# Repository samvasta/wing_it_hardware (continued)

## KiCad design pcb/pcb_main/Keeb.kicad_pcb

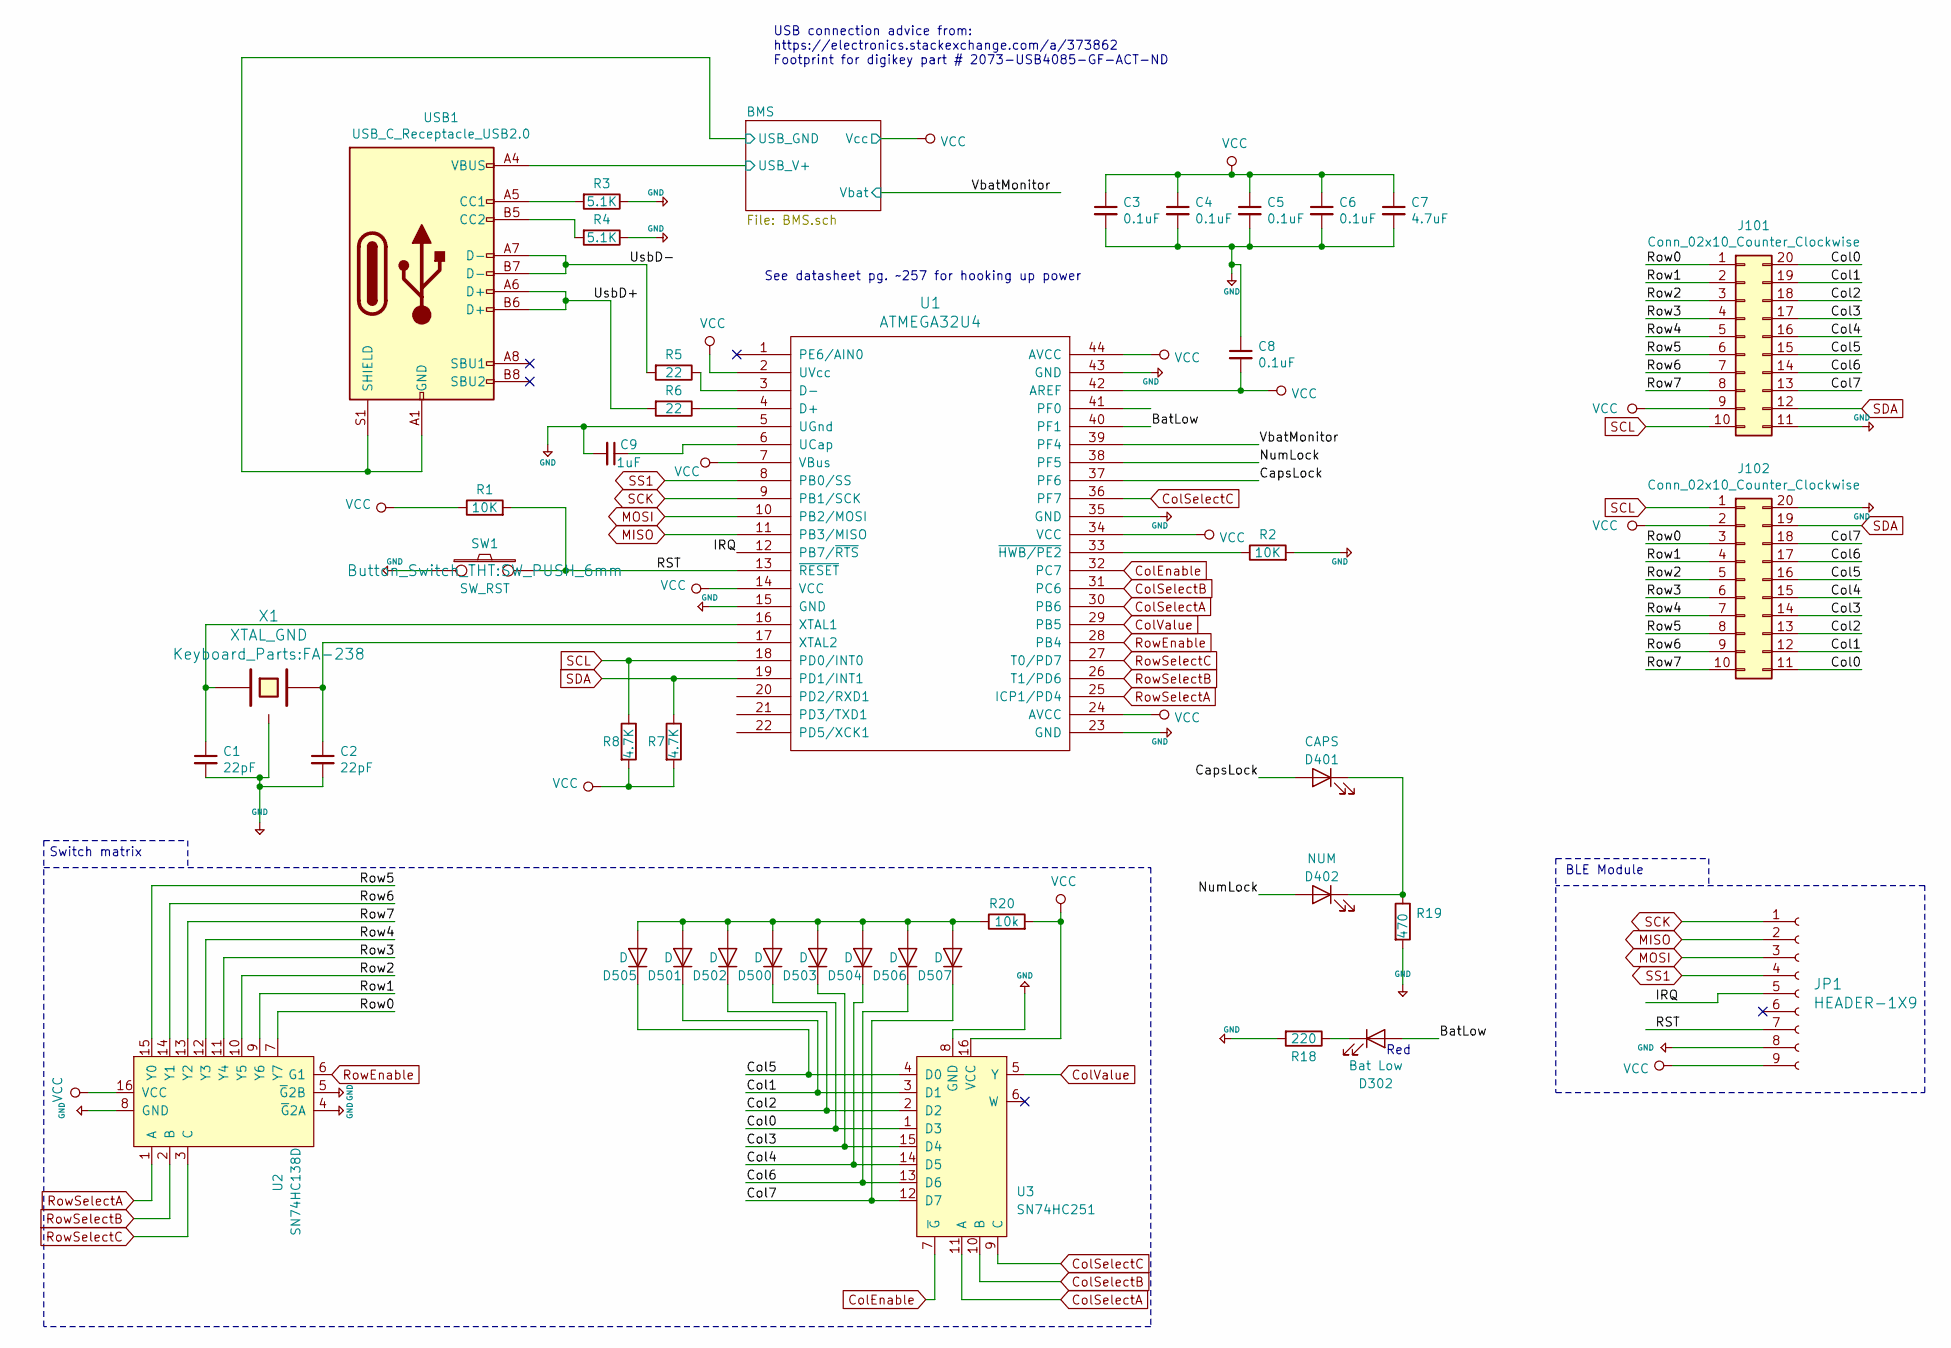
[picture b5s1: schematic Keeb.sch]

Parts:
C1, C2: 22pF; C_0805_2012Metric_Pad1.15x1.40mm_HandSolder
C3, C4, C5, C6, C8: 0.1uF; C_0805_2012Metric_Pad1.15x1.40mm_HandSolder
C7: 4.7uF; C_0805_2012Metric_Pad1.15x1.40mm_HandSolder
C9: 1uF; C_0805_2012Metric_Pad1.15x1.40mm_HandSolder
D302: Bat Low; LED_0805_2012Metric_Pad1.15x1.40mm_HandSolder
D401: CAPS; LED_0805_2012Metric_Pad1.15x1.40mm_HandSolder
D402: NUM; LED_0805_2012Metric_Pad1.15x1.40mm_HandSolder
D500, D501, D502, D503, D504, D505, D506, D507: D; D_0805_2012Metric_Pad1.15x1.40mm_HandSolder
J101, J102: Conn_02x10_Counter_Clockwise; Backplane_Connector_Hirose_PCN_20pos_Plug
JP1: HEADER-1X9; Adafruit_BLE_SPI_wire_tht
R1, R2: 10K; R_0805_2012Metric_Pad1.15x1.40mm_HandSolder
R3, R4: 5.1K; R_0805_2012Metric_Pad1.15x1.40mm_HandSolder
R5, R6: 22; R_0805_2012Metric_Pad1.15x1.40mm_HandSolder
R7, R8: 4.7K; R_0805_2012Metric_Pad1.15x1.40mm_HandSolder
R18: 220; R_0805_2012Metric_Pad1.15x1.40mm_HandSolder
R19: 470; R_0805_2012Metric_Pad1.15x1.40mm_HandSolder
R20: 10k; R_0805_2012Metric_Pad1.15x1.40mm_HandSolder
SW1: SW_RST; SW_PUSH_6mm
U1: ATMEGA32U4; ATMEGA32U4-AU
U2: SN74HC138D‎; SN74HC_package_d_soic
U3: SN74HC251; SN74HC_package_d_soic
USB1: USB_C_Receptacle_USB2.0; USB_C_Receptacle_GCT_USB4085
X1: XTAL_GND; FA-238

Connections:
/BMS/USB_V+: USB1.A4 (VBUS), USB1.A9 (VBUS), USB1.B4 (VBUS), USB1.B9 (VBUS); also elsewhere on the board
/BatLow: D302.2 (A), U1.40 (PF1)
/CapsLock: D401.2 (A), U1.37 (PF6)
/Col0: D500.1 (K), J101.20, J102.11, U3.1 (D3)
/Col1: D501.1 (K), J101.19, J102.12, U3.3 (D1)
/Col2: D502.1 (K), J101.18, J102.13, U3.2 (D2)
/Col3: D503.1 (K), J101.17, J102.14, U3.15 (D4)
/Col4: D504.1 (K), J101.16, J102.15, U3.14 (D5)
/Col5: D505.1 (K), J101.15, J102.16, U3.4 (D0)
/Col6: D506.1 (K), J101.14, J102.17, U3.13 (D6)
/Col7: D507.1 (K), J101.13, J102.18, U3.12 (D7)
/IRQ: JP1.5, U1.12 (PB7/~RTS)
/NumLock: D402.2 (A), U1.38 (PF5)
/RST: JP1.7, R1.2, SW1.2, U1.13 (~RESET)
/Row0: J101.1, J102.3, U2.7 (Y7)
/Row1: J101.2, J102.4, U2.9 (Y6)
/Row2: J101.3, J102.5, U2.10 (Y5)
/Row3: J101.4, J102.6, U2.11 (Y4)
/Row4: J101.5, J102.7, U2.12 (Y3)
/Row5: J101.6, J102.8, U2.15 (Y0)
/Row6: J101.7, J102.9, U2.14 (Y1)
/Row7: J101.8, J102.10, U2.13 (Y2)
/UsbD+: R6.2, USB1.A6 (D+), USB1.B6 (D+)
/UsbD-: R5.2, USB1.A7 (D-), USB1.B7 (D-)
/VbatMonitor: U1.39 (PF4); also elsewhere on the board
ColEnable: U1.32 (PC7), U3.7 (~G)
ColSelectA: U1.30 (PB6), U3.11 (A)
ColSelectB: U1.31 (PC6), U3.10 (B)
ColSelectC: U1.36 (PF7), U3.9 (C)
ColValue: U1.29 (PB5), U3.5 (Y)
GND: C1.2, C2.2, C3.2, C4.2, C5.2, C6.2, C7.2, C8.1, C9.2, J101.11, J102.20, JP1.8, R2.2, R3.1, R4.1, R18.2, R19.2, SW1.1, U1.5 (UGnd), U1.15 (GND), U1.23 (GND), U1.35 (GND), U1.43 (GND), U2.4 (~G~2A), U2.5 (~G~2B), U2.8 (GND), U3.8 (GND), USB1.A1 (GND), USB1.A12 (GND), USB1.B1 (GND), USB1.B12 (GND), USB1.S1 (SHIELD), X1.3; also elsewhere on the board
MISO: JP1.2, U1.11 (PB3/MISO)
MOSI: JP1.3, U1.10 (PB2/MOSI)
unnamed: C1.1, U1.16 (XTAL1), X1.1
unnamed: C2.1, U1.17 (XTAL2), X1.2
unnamed: C9.1, U1.6 (UCap)
unnamed: D302.1 (K), R18.1
unnamed: D401.1 (K), D402.1 (K), R19.1
unnamed: D500.2 (A), D501.2 (A), D502.2 (A), D503.2 (A), D504.2 (A), D505.2 (A), D506.2 (A), D507.2 (A), R20.1
unnamed: R2.1, U1.33 (~HWB/PE2)
unnamed: R3.2, USB1.A5 (CC1)
unnamed: R4.2, USB1.B5 (CC2)
unnamed: R5.1, U1.3 (D-)
unnamed: R6.1, U1.4 (D+)
RowEnable: U1.28 (PB4), U2.6 (G1)
RowSelectA: U1.25 (ICP1/PD4), U2.1 (A)
RowSelectB: U1.26 (T1/PD6), U2.2 (B)
RowSelectC: U1.27 (T0/PD7), U2.3 (C)
SCK: JP1.1, U1.9 (PB1/SCK)
SCL: J101.10, J102.1, R8.1, U1.18 (PD0/INT0)
SDA: J101.12, J102.19, R7.1, U1.19 (PD1/INT1)
SS1: JP1.4, U1.8 (PB0/SS)
VCC: C3.1, C4.1, C5.1, C6.1, C7.1, C8.2, J101.9, J102.2, JP1.9, R1.1, R7.2, R8.2, R20.2, U1.2 (UVcc), U1.7 (VBus), U1.14 (VCC), U1.24 (AVCC), U1.34 (VCC), U1.42 (AREF), U1.44 (AVCC), U2.16 (VCC), U3.16 (VCC); also elsewhere on the board

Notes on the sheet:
USB connection advice from: https://electronics.stackexchange.com/a/373862 Footprint for digikey part # 2073-USB4085-GF-ACT-ND
See datasheet pg. ~~257 for hooking up power
Switch matrix
BLE Module
Red

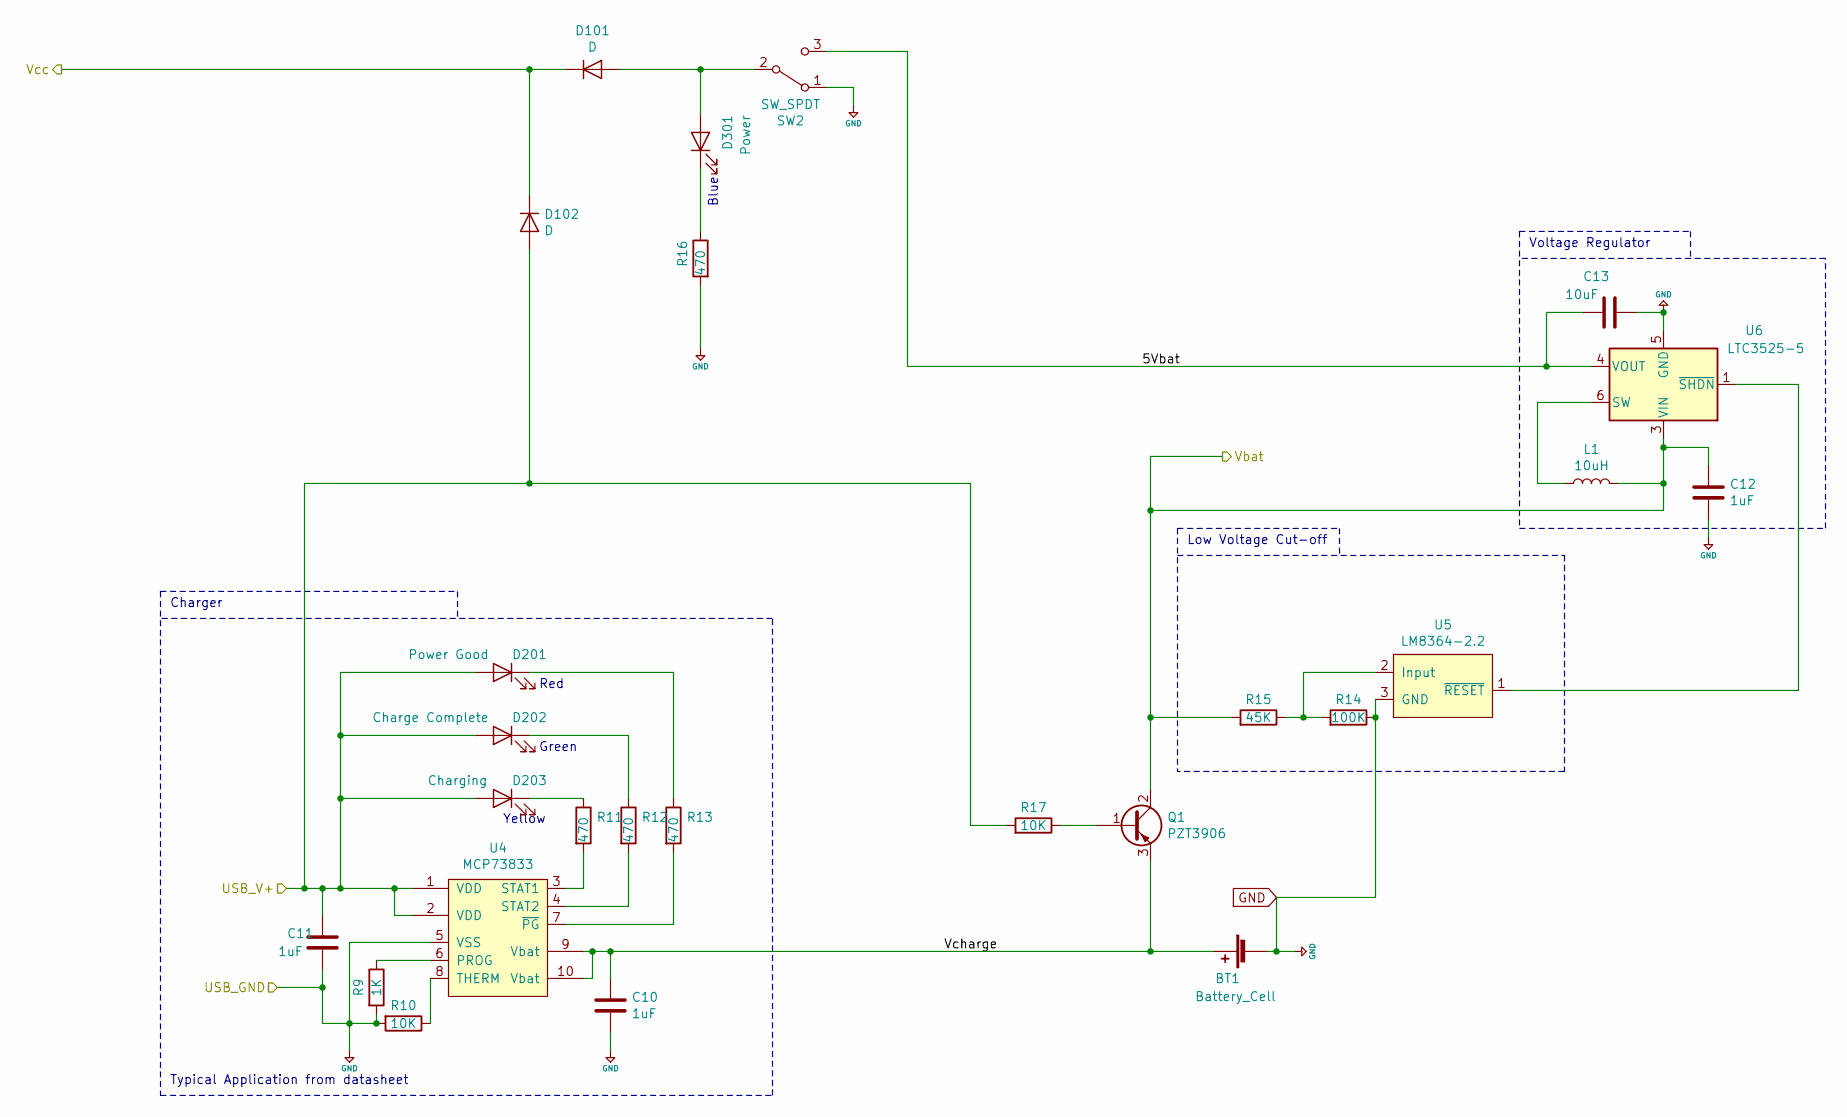
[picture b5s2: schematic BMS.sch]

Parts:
BT1: Battery_Cell; BatteryHolder_Keystone_1088_1xAA
C10, C11, C12: 1uF; C_0805_2012Metric_Pad1.15x1.40mm_HandSolder
C13: 10uF; C_0805_2012Metric_Pad1.15x1.40mm_HandSolder
D101, D102: D; D_MiniMELF_Handsoldering_Shorter_Pads
D201: Power Good; LED_0805_2012Metric_Pad1.15x1.40mm_HandSolder
D202: Charge Complete; LED_0805_2012Metric_Pad1.15x1.40mm_HandSolder
D203: Charging; LED_0805_2012Metric_Pad1.15x1.40mm_HandSolder
D301: Power; LED_0805_2012Metric_Pad1.15x1.40mm_HandSolder
L1: 10uH; L_0805_2012Metric_Pad1.15x1.40mm_HandSolder
Q1: PZT3906; SOT-223
R9: 1K; R_0805_2012Metric_Pad1.15x1.40mm_HandSolder
R10, R17: 10K; R_0805_2012Metric_Pad1.15x1.40mm_HandSolder
R11, R12, R13, R16: 470; R_0805_2012Metric_Pad1.15x1.40mm_HandSolder
R14: 100K; R_0805_2012Metric_Pad1.15x1.40mm_HandSolder
R15: 45K; R_0805_2012Metric_Pad1.15x1.40mm_HandSolder
SW2: SW_SPDT; SW_Slide_C&K_JS102011SAQN
U4: MCP73833; MCP73833T-AMI-UN
U5: LM8364-2.2; SOT-23-5_HandSoldering
U6: LTC3525-5; SOT-363_SC-70-6_Handsoldering

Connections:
/BMS/5Vbat: C13.2, SW2.3 (C), U6.4 (VOUT)
/BMS/USB_V+: C11.1, D102.2 (A), D201.2 (A), D202.2 (A), D203.2 (A), R17.2, U4.1 (VDD), U4.2 (VDD); also elsewhere on the board
/BMS/Vcharge: BT1.1 (+), C10.1, Q1.3 (E), U4.9 (Vbat), U4.10 (Vbat)
/VbatMonitor: C12.1, L1.1, Q1.2 (C), Q1.4 (C), R15.2, U6.3 (VIN); also elsewhere on the board
GND: BT1.2 (-), C10.2, C11.2, C12.2, C13.1, R9.2, R10.2, R14.1, R16.2, SW2.1 (A), U4.5 (VSS), U5.3 (GND), U6.2 (GND), U6.5 (GND); also elsewhere on the board
unnamed: D101.2 (A), D301.2 (A), SW2.2 (B)
unnamed: D201.1 (K), R13.1
unnamed: D202.1 (K), R12.1
unnamed: D203.1 (K), R11.1
unnamed: D301.1 (K), R16.1
unnamed: L1.2, U6.6 (SW)
unnamed: Q1.1 (B), R17.1
unnamed: R9.1, U4.6 (PROG)
unnamed: R10.1, U4.8 (THERM)
unnamed: R11.2, U4.3 (STAT1)
unnamed: R12.2, U4.4 (STAT2)
unnamed: R13.2, U4.7 (~PG)
unnamed: R14.2, R15.1, U5.2 (Input)
unnamed: U5.1 (~RESET), U6.1 (~SHDN)
VCC: D101.1 (K), D102.1 (K); also elsewhere on the board

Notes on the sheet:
Typical Application from datasheet
Charger
Low Voltage Cut-off
Green
Red
Yellow
Blue
Voltage Regulator

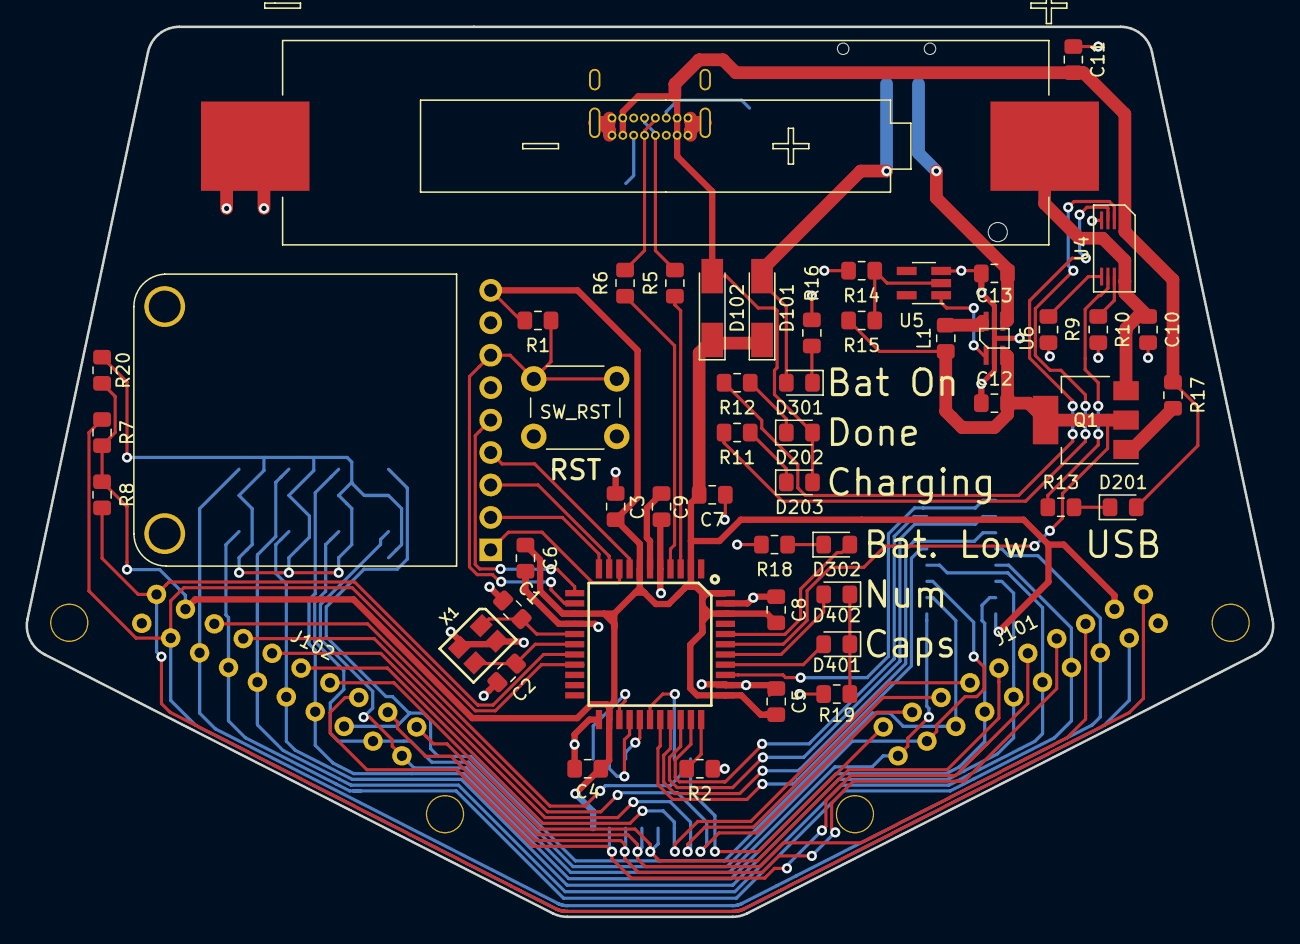
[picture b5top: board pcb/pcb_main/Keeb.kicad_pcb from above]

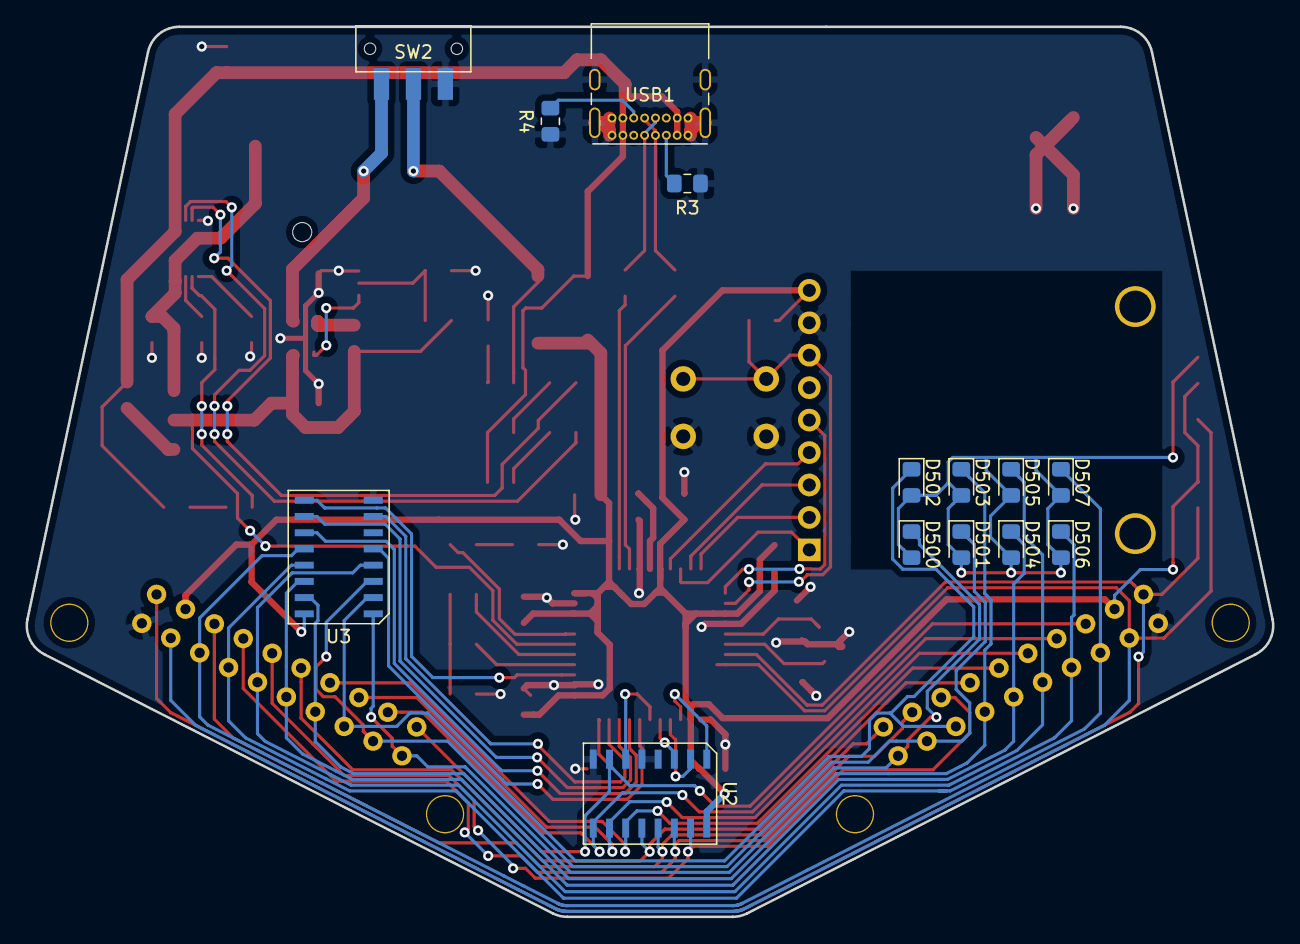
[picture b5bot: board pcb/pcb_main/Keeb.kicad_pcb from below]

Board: 2 copper layers, 97.6 x 69.7 mm, 66 parts (15 on the bottom side), 69 nets.

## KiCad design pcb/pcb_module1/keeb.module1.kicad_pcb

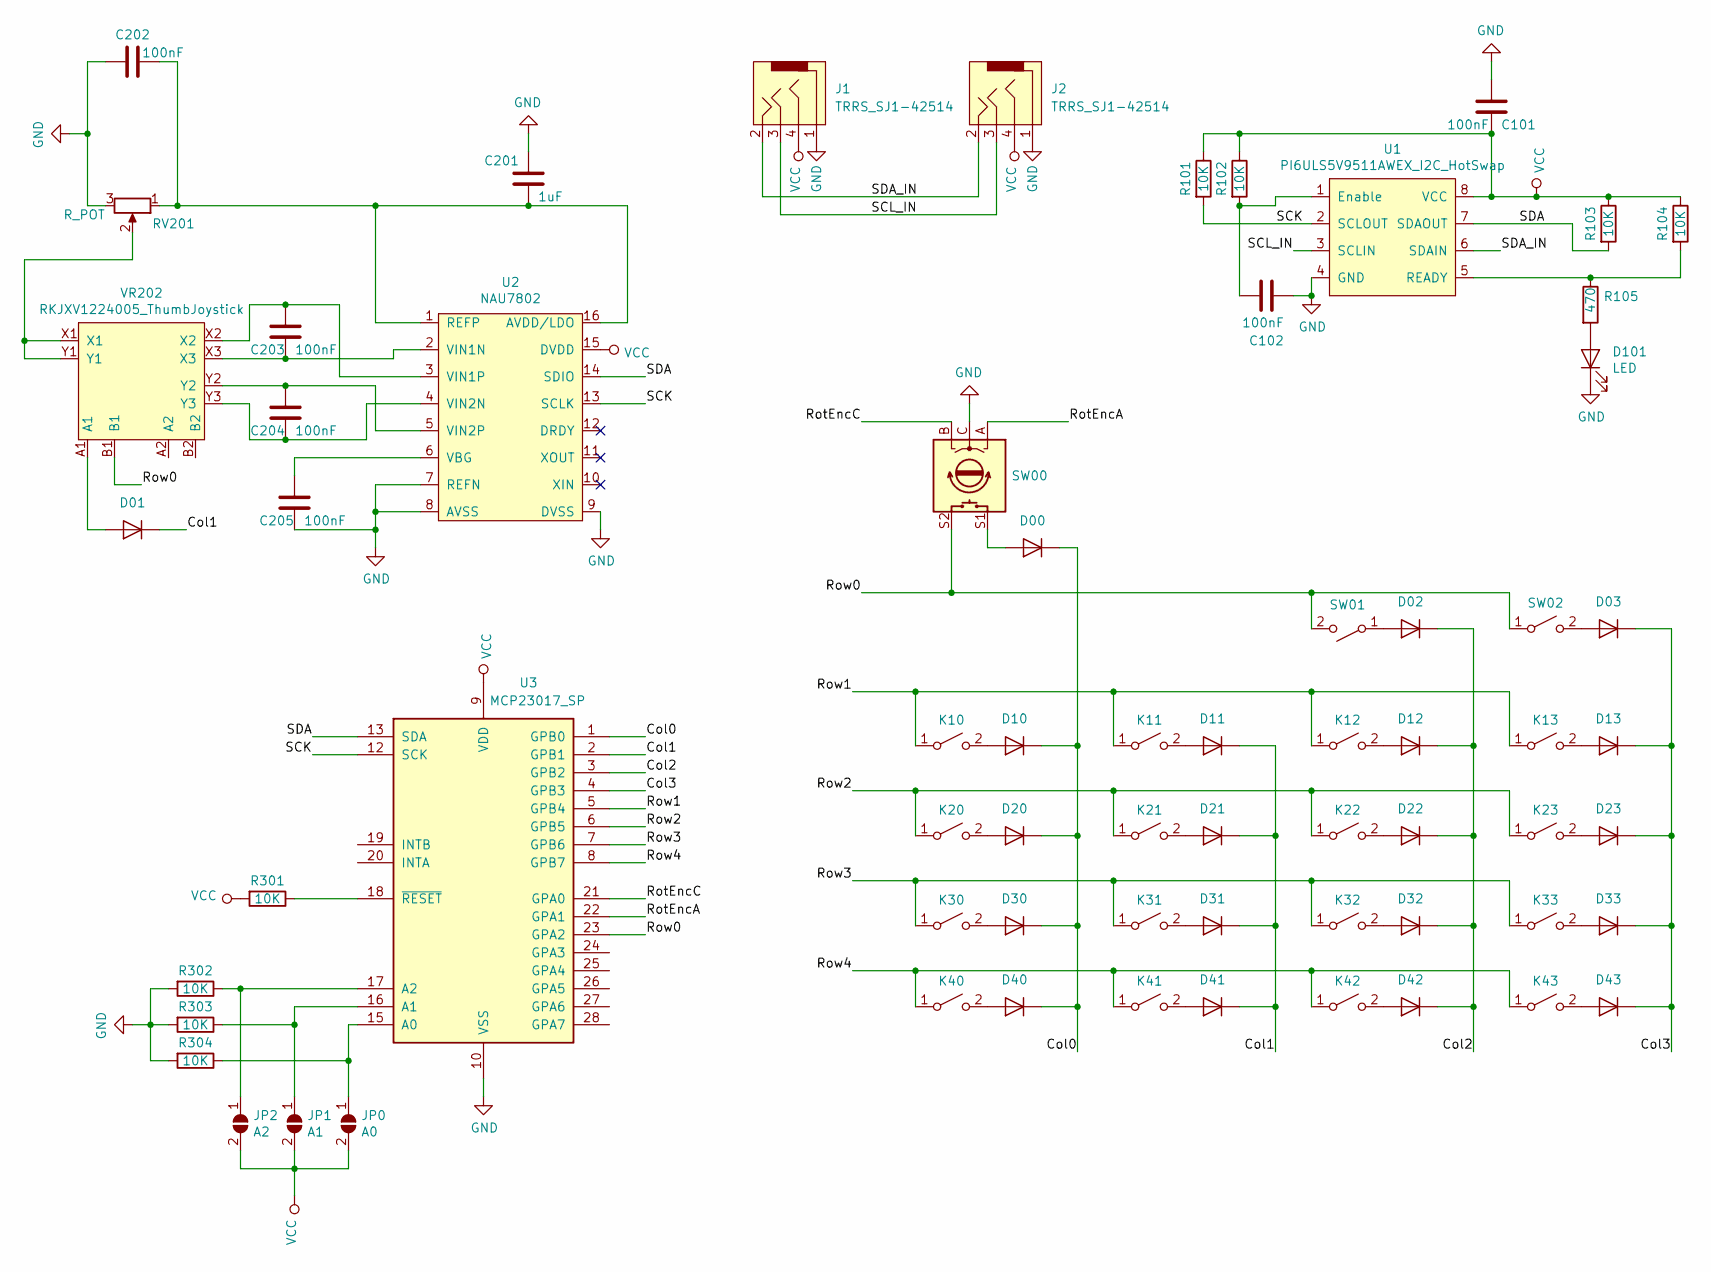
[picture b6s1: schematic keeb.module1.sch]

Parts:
C101, C102, C202, C203, C204, C205: 100nF; C_0805_2012Metric_Pad1.15x1.40mm_HandSolder
C201: 1uF; C_0805_2012Metric_Pad1.15x1.40mm_HandSolder
D00, D01, D02, D03, D10, D11, D12, D13, D20, D21, D22, D23, D30, D31, D32, D33, D40, D41, D42, D43: D; D_A-405_P7.62mm_Horizontal
D101: LED; D_0805_2012Metric_Pad1.15x1.40mm_HandSolder
J1, J2: TRRS_SJ1-42514; 3.5mm_Cut_out
JP0: A0; SolderJumper-2_P1.3mm_Open_RoundedPad1.0x1.5mm
JP1: A1; SolderJumper-2_P1.3mm_Open_RoundedPad1.0x1.5mm
JP2: A2; SolderJumper-2_P1.3mm_Open_RoundedPad1.0x1.5mm
K10, K11, K12, K13, K20, K21, K22, K23, K30, K31, K32, K33, K40, K41, K42, K43: SW_SPST; Kailh_socket_vias
R101, R102, R103, R104, R301, R302, R303, R304: 10K; Resistor-Compact
R105: 470; Resistor-Compact
RV201: R_POT; SlidePot_PS45M
SW00: Rotary_Encoder_Switch; PEC12R-4xxxF-Sxxxx_Rotary_Encoder
SW01, SW02: SW_SPST; B3J-1100_Switch
U1: PI6ULS5V9511AWEX_I2C_HotSwap; PI6ULS5V9511A_I2C_HotSwap
U2: NAU7802; DIP-16_W7.62mm
U3: MCP23017_SP; DIP-28_W7.62mm
VR202: RKJXV1224005_ThumbJoystick; RKJXV1224_AnalogJoystick

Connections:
/Col0: D00.1 (K), D10.1 (K), D20.1 (K), D30.1 (K), D40.1 (K), U3.1 (GPB0)
/Col1: D01.1 (K), D11.1 (K), D21.1 (K), D31.1 (K), D41.1 (K), U3.2 (GPB1)
/Col2: D02.1 (K), D12.1 (K), D22.1 (K), D32.1 (K), D42.1 (K), U3.3 (GPB2)
/Col3: D03.1 (K), D13.1 (K), D23.1 (K), D33.1 (K), D43.1 (K), U3.4 (GPB3)
/RotEncA: SW00.A, U3.22 (GPA1)
/RotEncC: SW00.B, U3.21 (GPA0)
/Row0: SW00.S2, SW01.2 (B), SW02.1 (A), U3.23 (GPA2), VR202.B1
/Row1: K10.1 (A), K11.1 (A), K12.1 (A), K13.1 (A), U3.5 (GPB4)
/Row2: K20.1 (A), K21.1 (A), K22.1 (A), K23.1 (A), U3.6 (GPB5)
/Row3: K30.1 (A), K31.1 (A), K32.1 (A), K33.1 (A), U3.7 (GPB6)
/Row4: K40.1 (A), K41.1 (A), K42.1 (A), K43.1 (A), U3.8 (GPB7)
/SCK: R101.2, U1.2 (SCLOUT), U2.13 (SCLK), U3.12 (SCK)
/SCL_IN: J1.3, J2.3, U1.3 (SCLIN)
/SDA: R103.2, U1.7 (SDAOUT), U2.14 (SDIO), U3.13 (SDA)
/SDA_IN: J1.2, J2.2, U1.6 (SDAIN)
GND: C101.1, C102.2, C201.1, C202.2, C205.2, D101.1 (K), J1.1, J2.1, R302.2, R303.2, R304.2, RV201.3, SW00.C, U1.4 (GND), U2.7 (REFN), U2.8 (AVSS), U2.9 (DVSS), U3.10 (VSS)
unnamed: C102.1, R102.2, U1.1 (Enable)
unnamed: C201.2, C202.1, RV201.1, U2.1 (REFP), U2.16 (AVDD/LDO)
unnamed: C203.1, U2.3 (VIN1P), VR202.X2
unnamed: C203.2, U2.2 (VIN1N), VR202.X3
unnamed: C204.1, U2.5 (VIN2P), VR202.Y2
unnamed: C204.2, U2.4 (VIN2N), VR202.Y3
unnamed: C205.1, U2.6 (VBG)
unnamed: D00.2 (A), SW00.S1
unnamed: D01.2 (A), VR202.A1
unnamed: D02.2 (A), SW01.1 (A)
unnamed: D03.2 (A), SW02.2 (B)
unnamed: D10.2 (A), K10.2 (B)
unnamed: D11.2 (A), K11.2 (B)
unnamed: D12.2 (A), K12.2 (B)
unnamed: D13.2 (A), K13.2 (B)
unnamed: D20.2 (A), K20.2 (B)
unnamed: D21.2 (A), K21.2 (B)
unnamed: D22.2 (A), K22.2 (B)
unnamed: D23.2 (A), K23.2 (B)
unnamed: D30.2 (A), K30.2 (B)
unnamed: D31.2 (A), K31.2 (B)
unnamed: D32.2 (A), K32.2 (B)
unnamed: D33.2 (A), K33.2 (B)
unnamed: D40.2 (A), K40.2 (B)
unnamed: D41.2 (A), K41.2 (B)
unnamed: D42.2 (A), K42.2 (B)
unnamed: D43.2 (A), K43.2 (B)
unnamed: D101.2 (A), R105.2
unnamed: JP0.1 (A), R304.1, U3.15 (A0)
unnamed: JP1.1 (A), R303.1, U3.16 (A1)
unnamed: JP2.1 (A), R302.1, U3.17 (A2)
unnamed: R104.2, R105.1, U1.5 (READY)
unnamed: R301.1, U3.18 (~RESET~)
unnamed: RV201.2, VR202.X1, VR202.Y1
VCC: C101.2, J1.4, J2.4, JP0.2 (B), JP1.2 (B), JP2.2 (B), R101.1, R102.1, R103.1, R104.1, R301.2, U1.8 (VCC), U2.15 (DVDD), U3.9 (VDD)

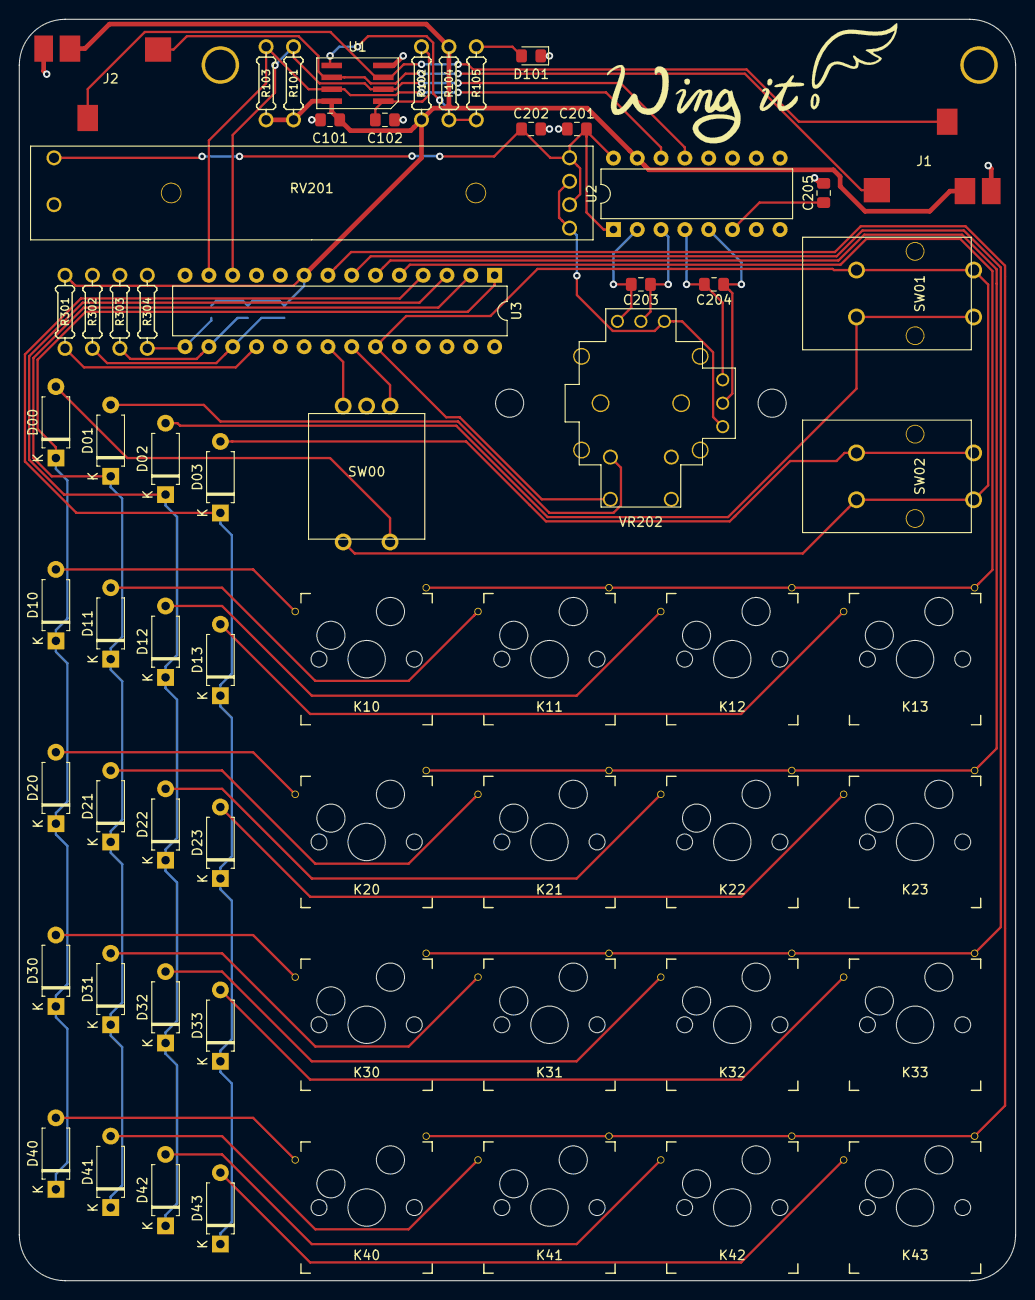
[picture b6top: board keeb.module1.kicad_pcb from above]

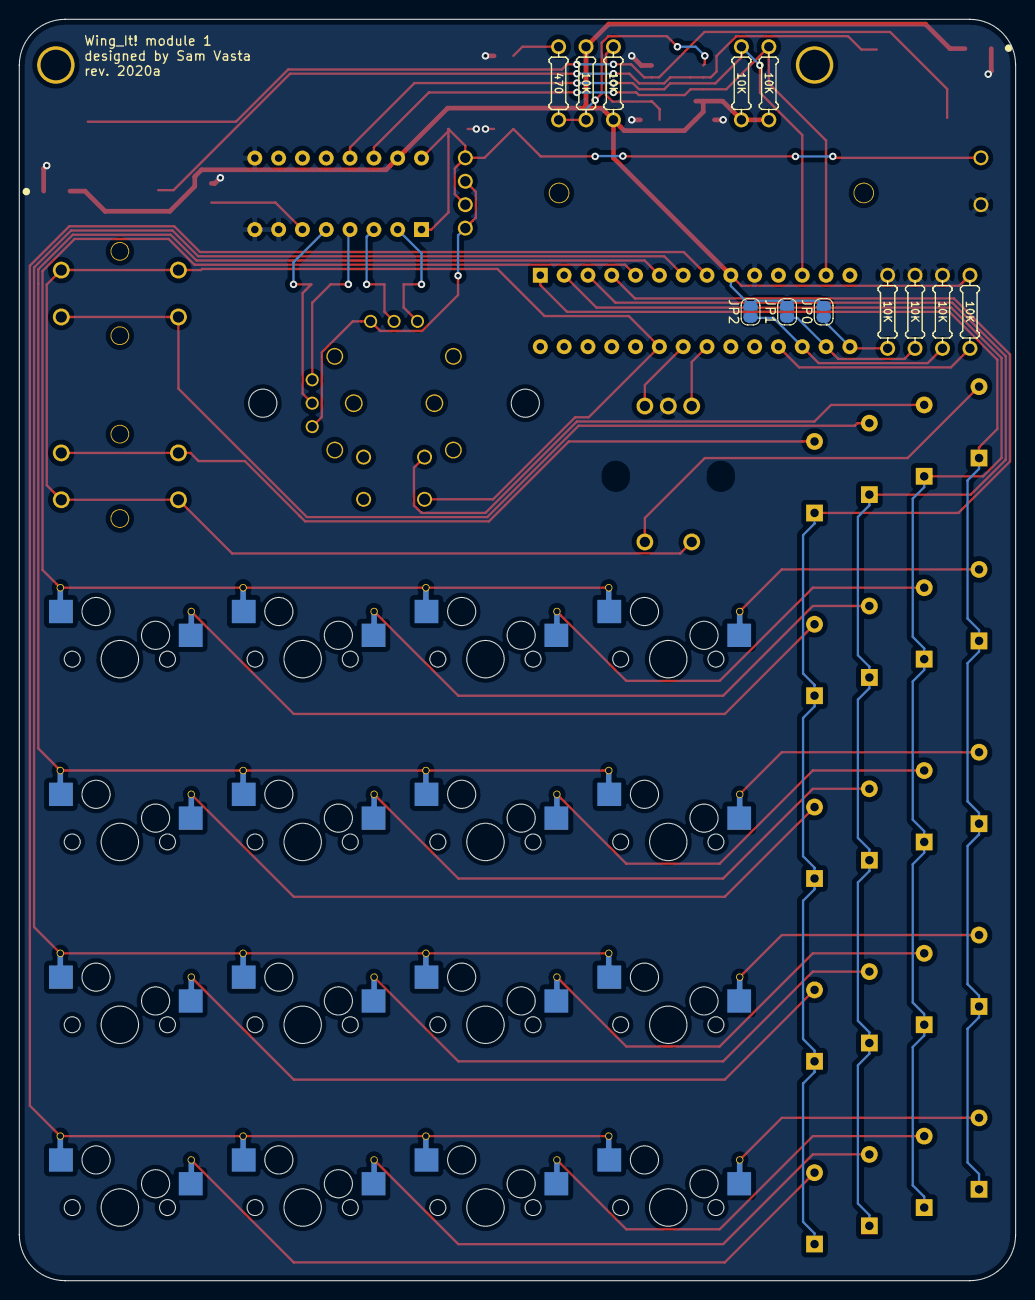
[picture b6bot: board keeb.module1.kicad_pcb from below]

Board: 2 copper layers, 106.3 x 134.6 mm, 66 parts (14 on the bottom side), 51 nets.

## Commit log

2020-03-28 Fixed some mistakes in logic/layout from v1
2020-03-28 Added specs doc. for cad files
2020-03-28 Started minimal design cad drawing
2020-03-29 Most pcb of layout done
2020-03-29 Moved custom symbols & footprints into git submodules
2020-03-31 More layout work
2020-03-31 Layout & cad work for split pcb design
2020-04-02 First pass at split pcb design completed
2020-04-05 Completed first revision of module1, started on module 2
2020-04-05 Rev 1 of module 2 & updated all-in-one cad drawing
2020-04-14 Added dxf files to cut top/bottom plates
2020-04-18 Updated connection method on main pcb
2020-05-02 Updated layout to use hirose connectors
2020-05-28 bms changes
2020-08-21 Minor changes and started trackball module
2020-09-16 Fixed layout to support trackball over SPI
2020-09-16 Removed most keys to prepare for test PCB
2020-09-20 Disabled keebio library
2020-11-18 Fixed overlapping nets
2020-11-19 Fixed issues from test branch
2020-11-20 restarted layout
2020-11-20 Finished new layout
2020-11-21 small tweaks
2020-11-22 Split board and shield into separate projects
2020-11-25 Fixed DRC errors
2020-11-25 updaaaaaaates
2020-11-26 updated cad files
2020-12-12 Changed i/o expander to ssop package
2020-12-12 cad updates
2020-12-12 Cleaned up cad folder
2020-12-12 added cad file
2020-12-12 Added inventor files
2020-12-22 Fixed right-hand i2c connection issue
2020-12-22 Exported top & bottom plate DXFs for mfr
2020-12-22 Modified OLED mounting holes to fit M2 screws
2021-02-04 Created dxf for manufacture + added docs
2021-02-04 Modified shield to make i2c & usb connections solderless
2021-02-04 updated kicad resources
